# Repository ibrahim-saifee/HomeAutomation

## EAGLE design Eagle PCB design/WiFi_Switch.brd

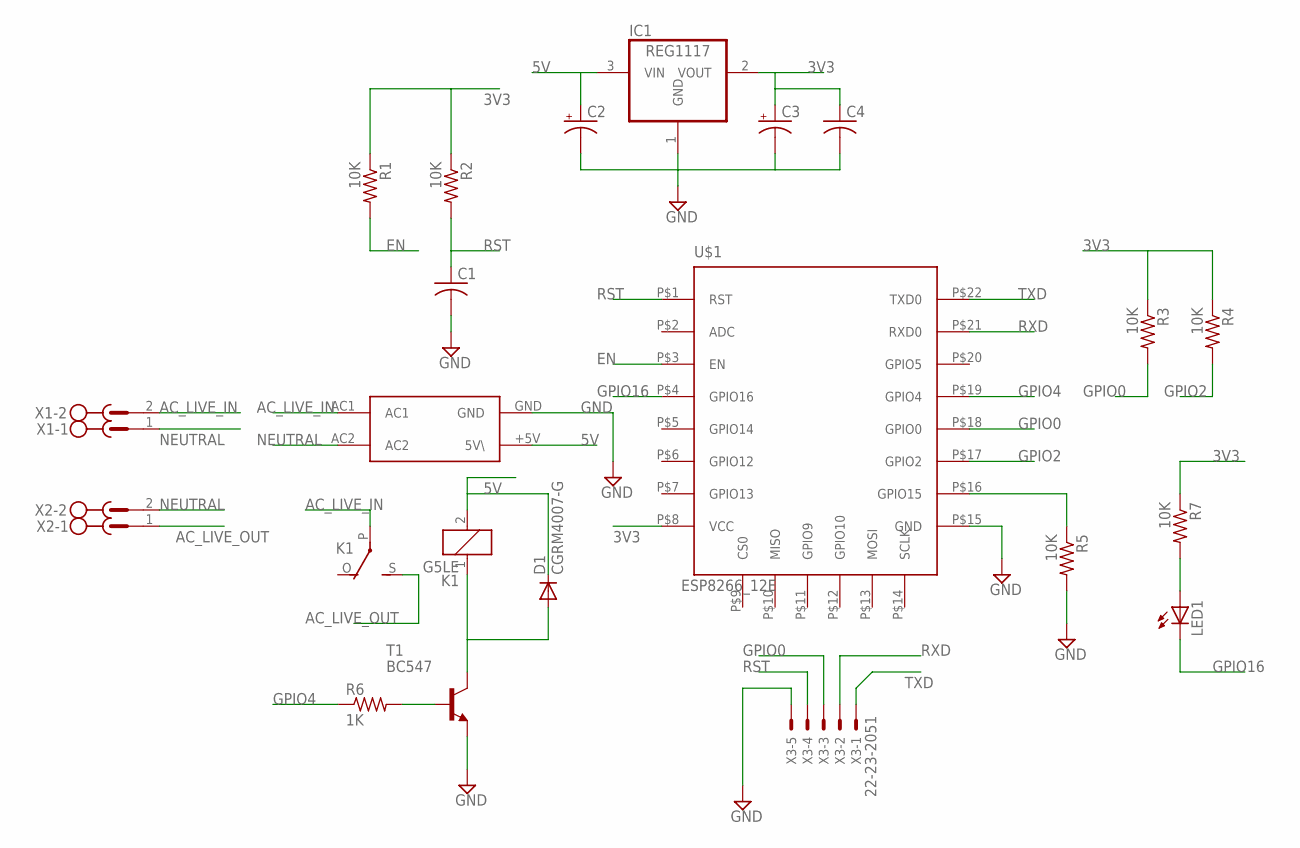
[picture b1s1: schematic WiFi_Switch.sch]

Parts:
C1, C4: C-USC1206; C1206
C2, C3: CPOL-USE5-6; E5-6
D1: CGRM4007-G; SOD-123_MINI-SMA
IC1: REG1117; SOT223
K1: G5LE
LED1: LED3MM
R1, R2, R3, R4, R5, R7: 10K; R1206
R6: 1K; R1206
T1: BC547; TO92
U$1: ESP8266_12E; SMT_ESP8266
U$2: HILINK_SMPS_5V5W; PCB_MOUNT
X1, X2: MSTBV2
X3: 22-23-2051

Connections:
3V3: C3.+, C4.1, IC1.2 (VOUT), R1.1, R2.1, R3.1, R4.1, R7.1, U$1.P$8 (VCC)
5V: C2.+, D1.C, IC1.3 (VIN), K1.2, U$2.+5V (5V\)
AC_LIVE_IN: K1.P, U$2.AC1, X1.2
AC_LIVE_OUT: K1.S, X2.1
EN: R1.2, U$1.P$3 (EN)
GND: C1.2, C2.-, C3.-, C4.2, IC1.1 (GND), R5.2, T1.1 (E), U$1.P$15 (GND), U$2.GND, X3.5
GPIO0: R3.2, U$1.P$18 (GPIO0), X3.3
GPIO2: R4.2, U$1.P$17 (GPIO2)
GPIO4: R6.1, U$1.P$19 (GPIO4)
GPIO16: LED1.K (C), U$1.P$4 (GPIO16)
unnamed: R5.1, U$1.P$16 (GPIO15)
unnamed: R6.2, T1.2 (B)
unnamed: D1.A, K1.1, T1.3 (C)
unnamed: LED1.A, R7.2
NEUTRAL: U$2.AC2, X1.1, X2.2
RST: C1.1, R2.2, U$1.P$1 (RST), X3.4
RXD: U$1.P$21 (RXD0), X3.2
TXD: U$1.P$22 (TXD0), X3.1

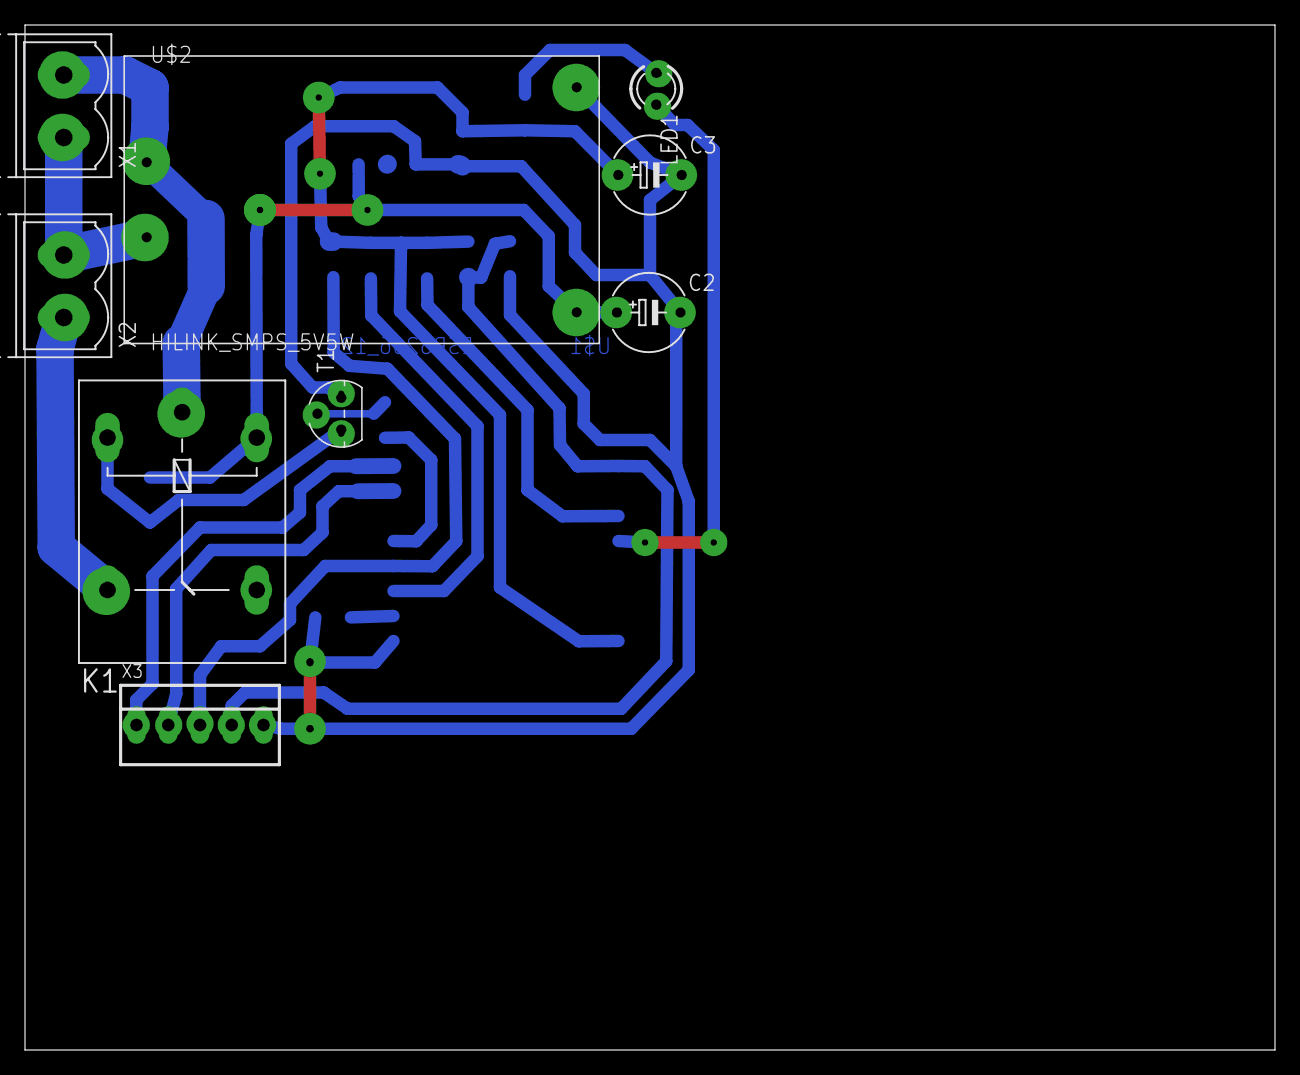
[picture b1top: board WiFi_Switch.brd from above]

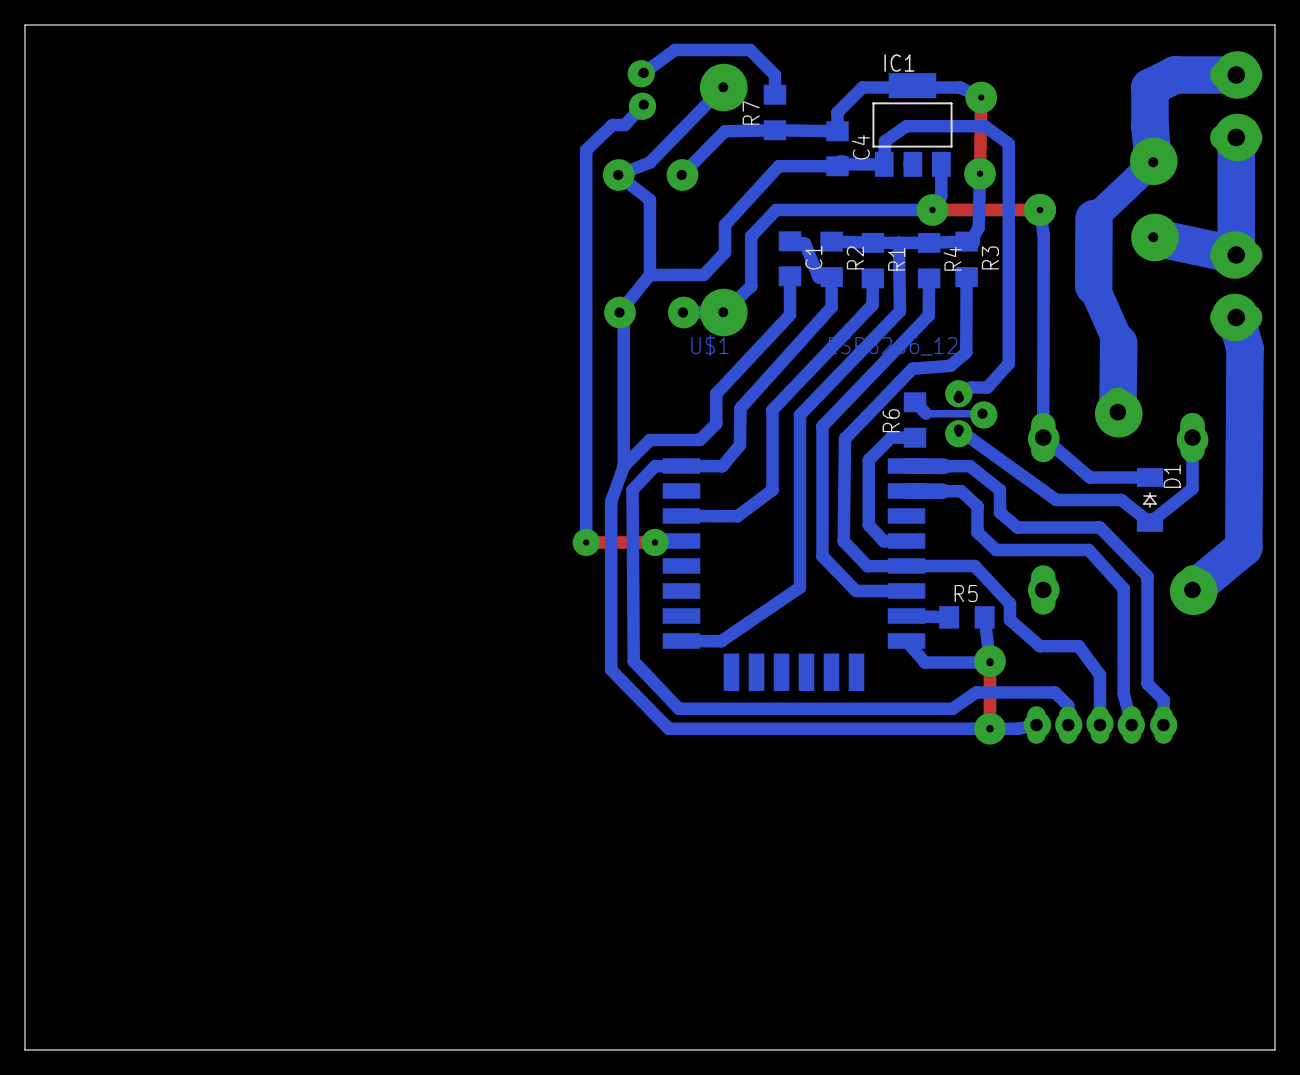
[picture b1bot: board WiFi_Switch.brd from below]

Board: 2 copper layers, 100.0 x 82.0 mm, 21 parts (12 on the bottom side), 18 nets.
